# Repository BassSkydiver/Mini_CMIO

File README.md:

# CMIOBoard
A tiny, compact IO board for the raspberry compute modules 1/3/3+

## Features:
IO Ports:  
* USB-C (Power/USB 2.0)
* HDMI
* USB-Micro B (Slave port)
* Dual-USB-A 2.0
* Ethernet

## Other:
* Three pin 5V fan header
* Three pin boot selector
* 40 pin standard Raspberry Pi GPIO
* 4x2.2mm mounting holes
* Power LED (Red)
* Boot LED (Green)

## Dimensions:
75.66mm x 65.63mm  
2.844mm radius rounded corners
2.2mm diameter mounting holes (M2 or US #1/2 screws)  
69.97mm center distance between horizontally aligned mounting holes.  
59.94mm center distance between vertically aligned mounting holes.  
## Important!
The Raspberry Pi Compute Module requires a 5v, 2+ Amp power supply. (5.1V Recommended)
This board was made by a complete amatuer and should be avoided or subject to harsh scrutiny before used in a real application.

## Directions to Install:
1. Make sure your KiCAD verison is 7.0.6 or higher
2. Rename the "Footprints" folder to "Footprints.pretty"
3. Open the "RPCM1 IO Board.kicad_pro" file
4. Add symbols and footprints from this directory into the "Project Specific Libraries" section of the Symbol Library Manager and the Footprint Library Manager
5. Do whatever you want I guess :)

*License: GNU General Public License v3.0*  
*[gnu.org/licenses/gpl-3.0](https://www.gnu.org/licenses/gpl-3.0.en.html)*

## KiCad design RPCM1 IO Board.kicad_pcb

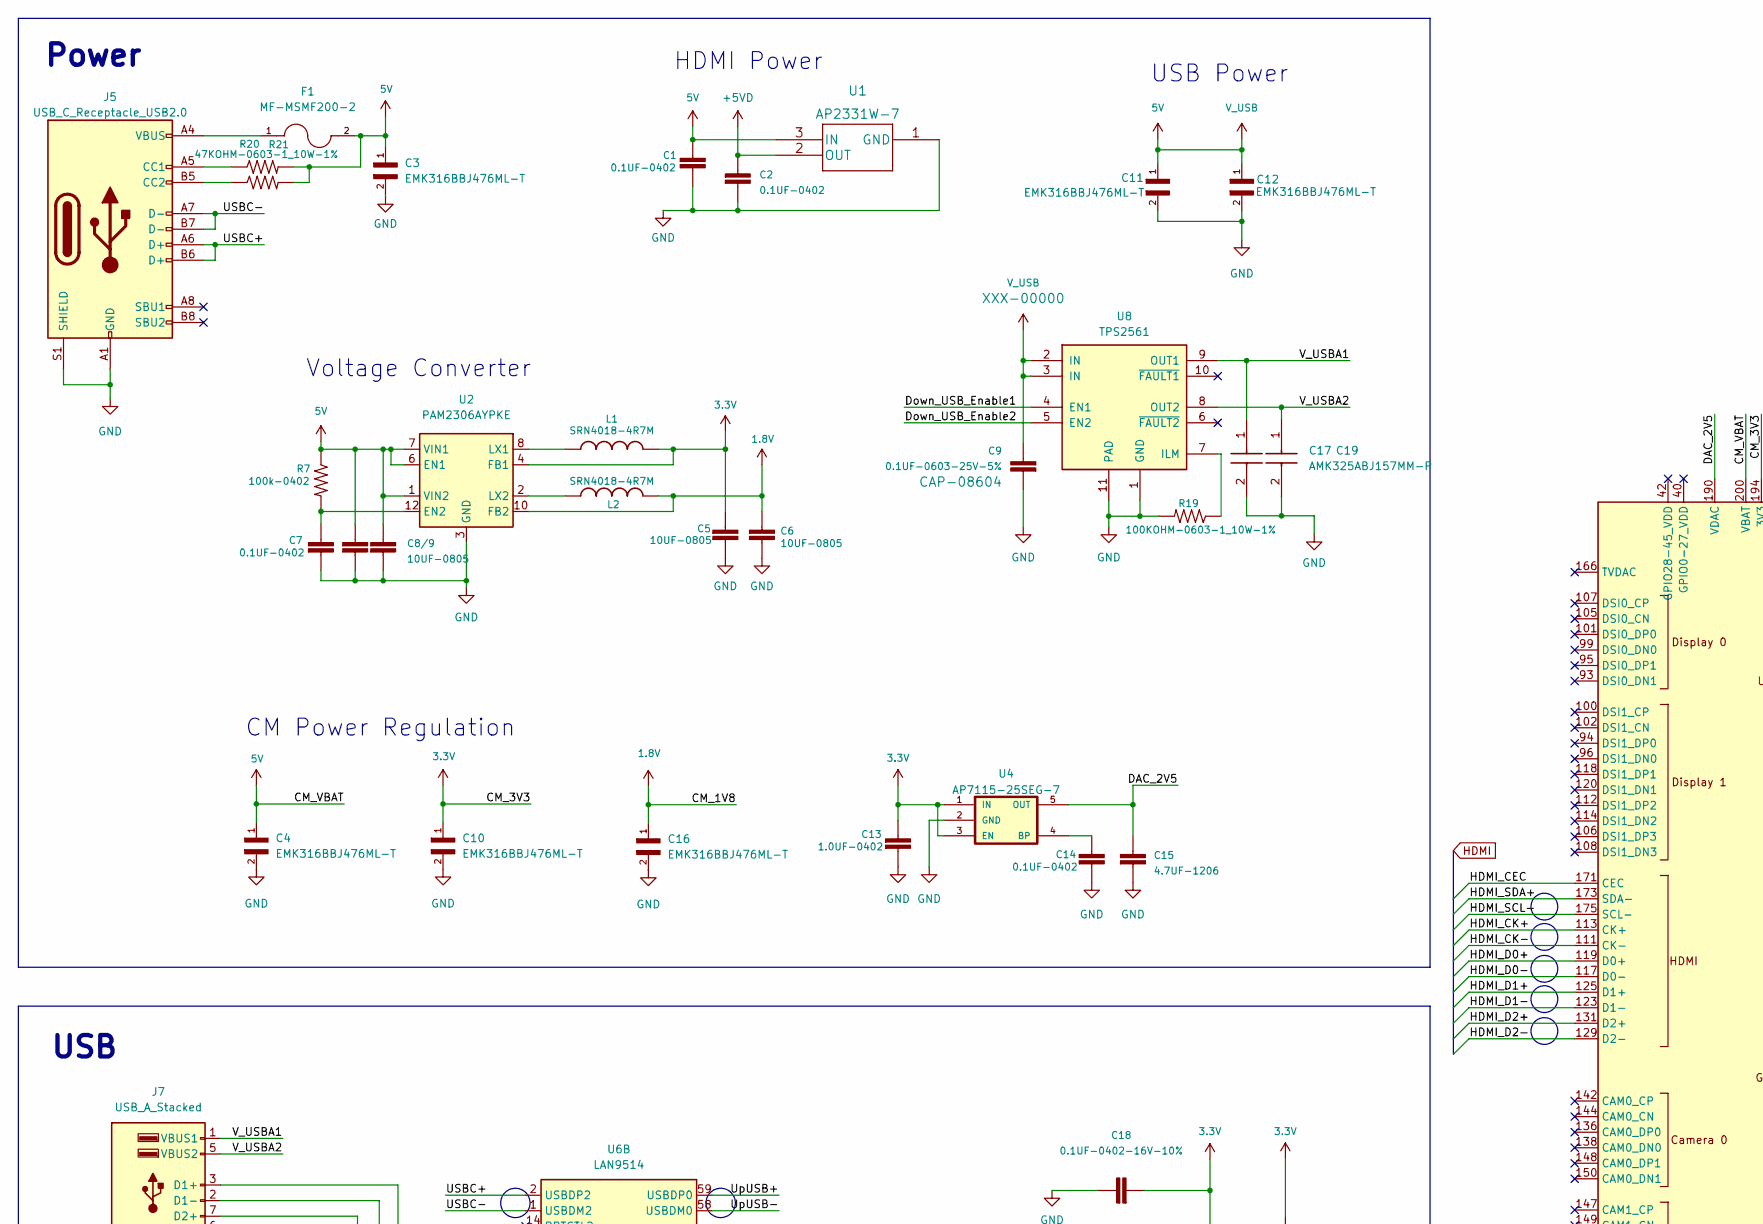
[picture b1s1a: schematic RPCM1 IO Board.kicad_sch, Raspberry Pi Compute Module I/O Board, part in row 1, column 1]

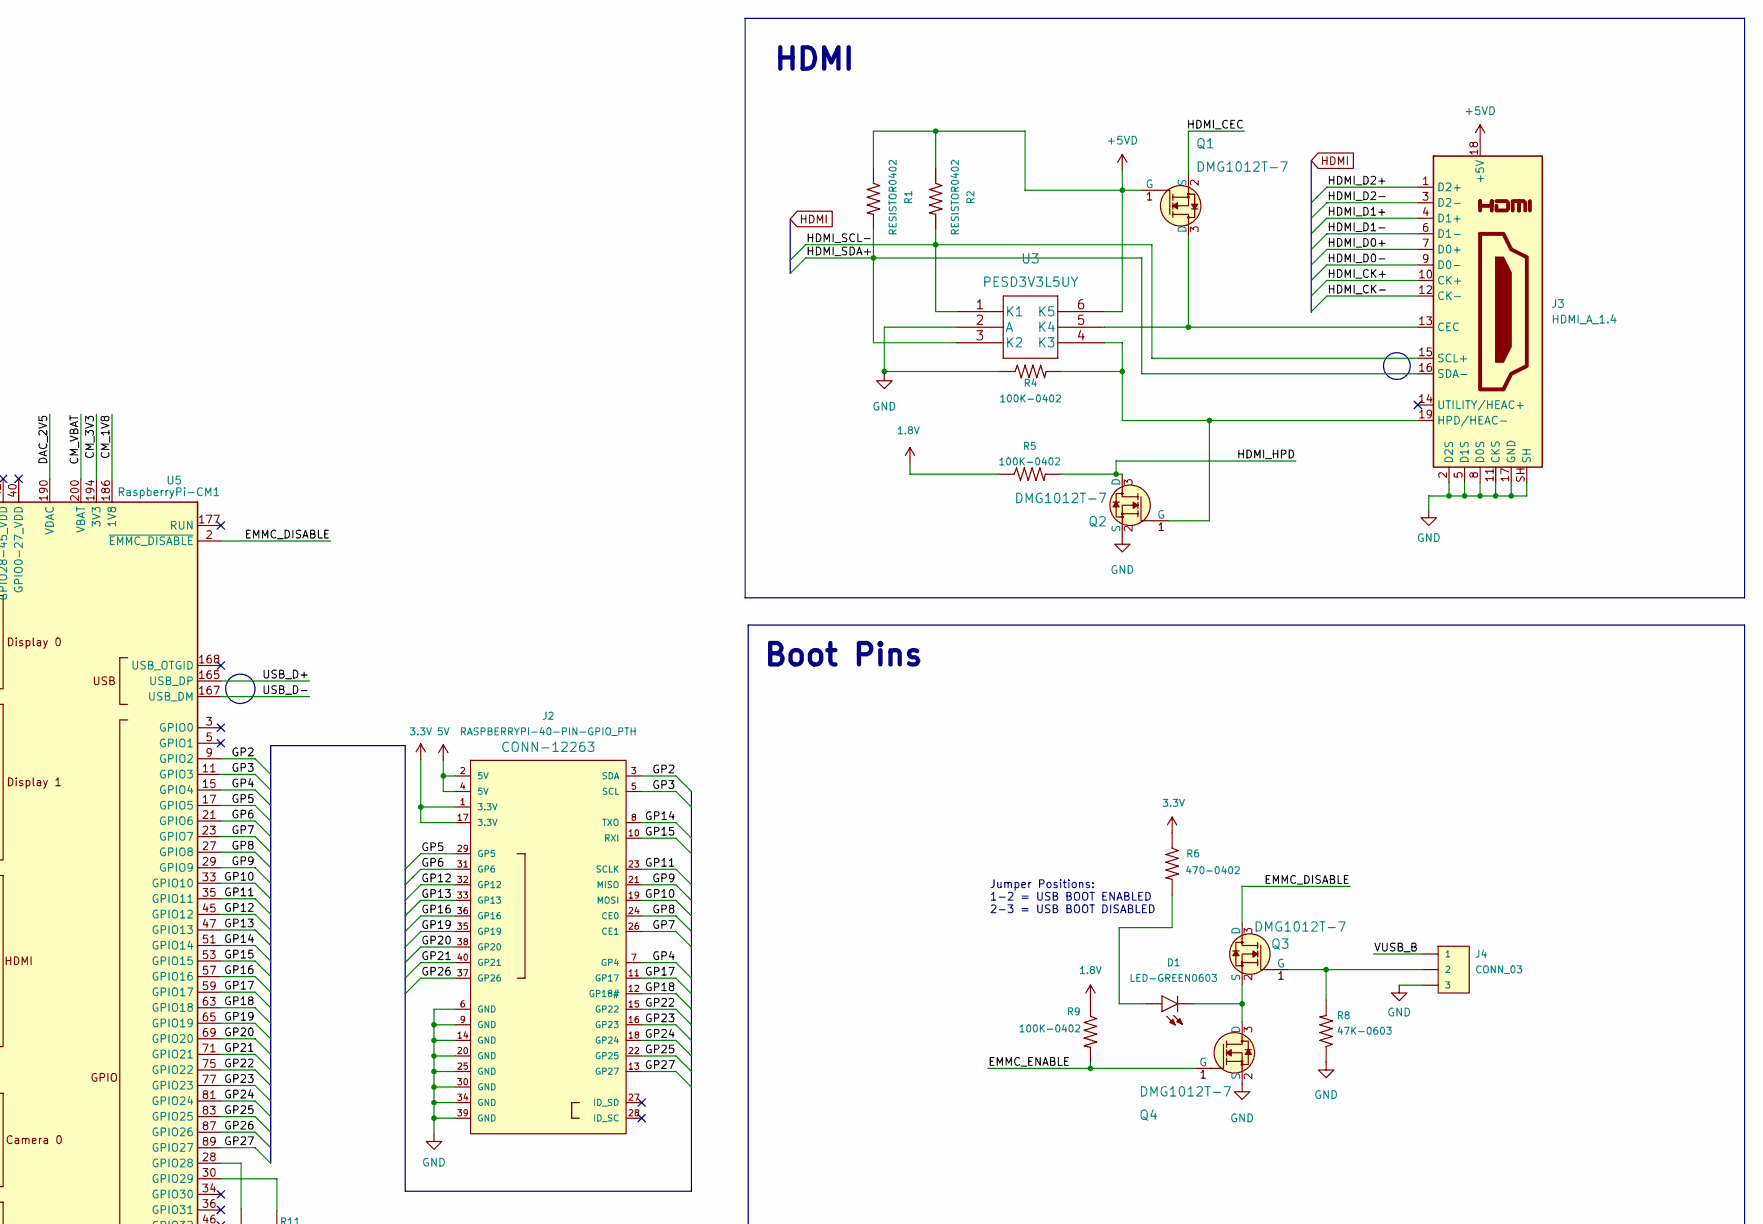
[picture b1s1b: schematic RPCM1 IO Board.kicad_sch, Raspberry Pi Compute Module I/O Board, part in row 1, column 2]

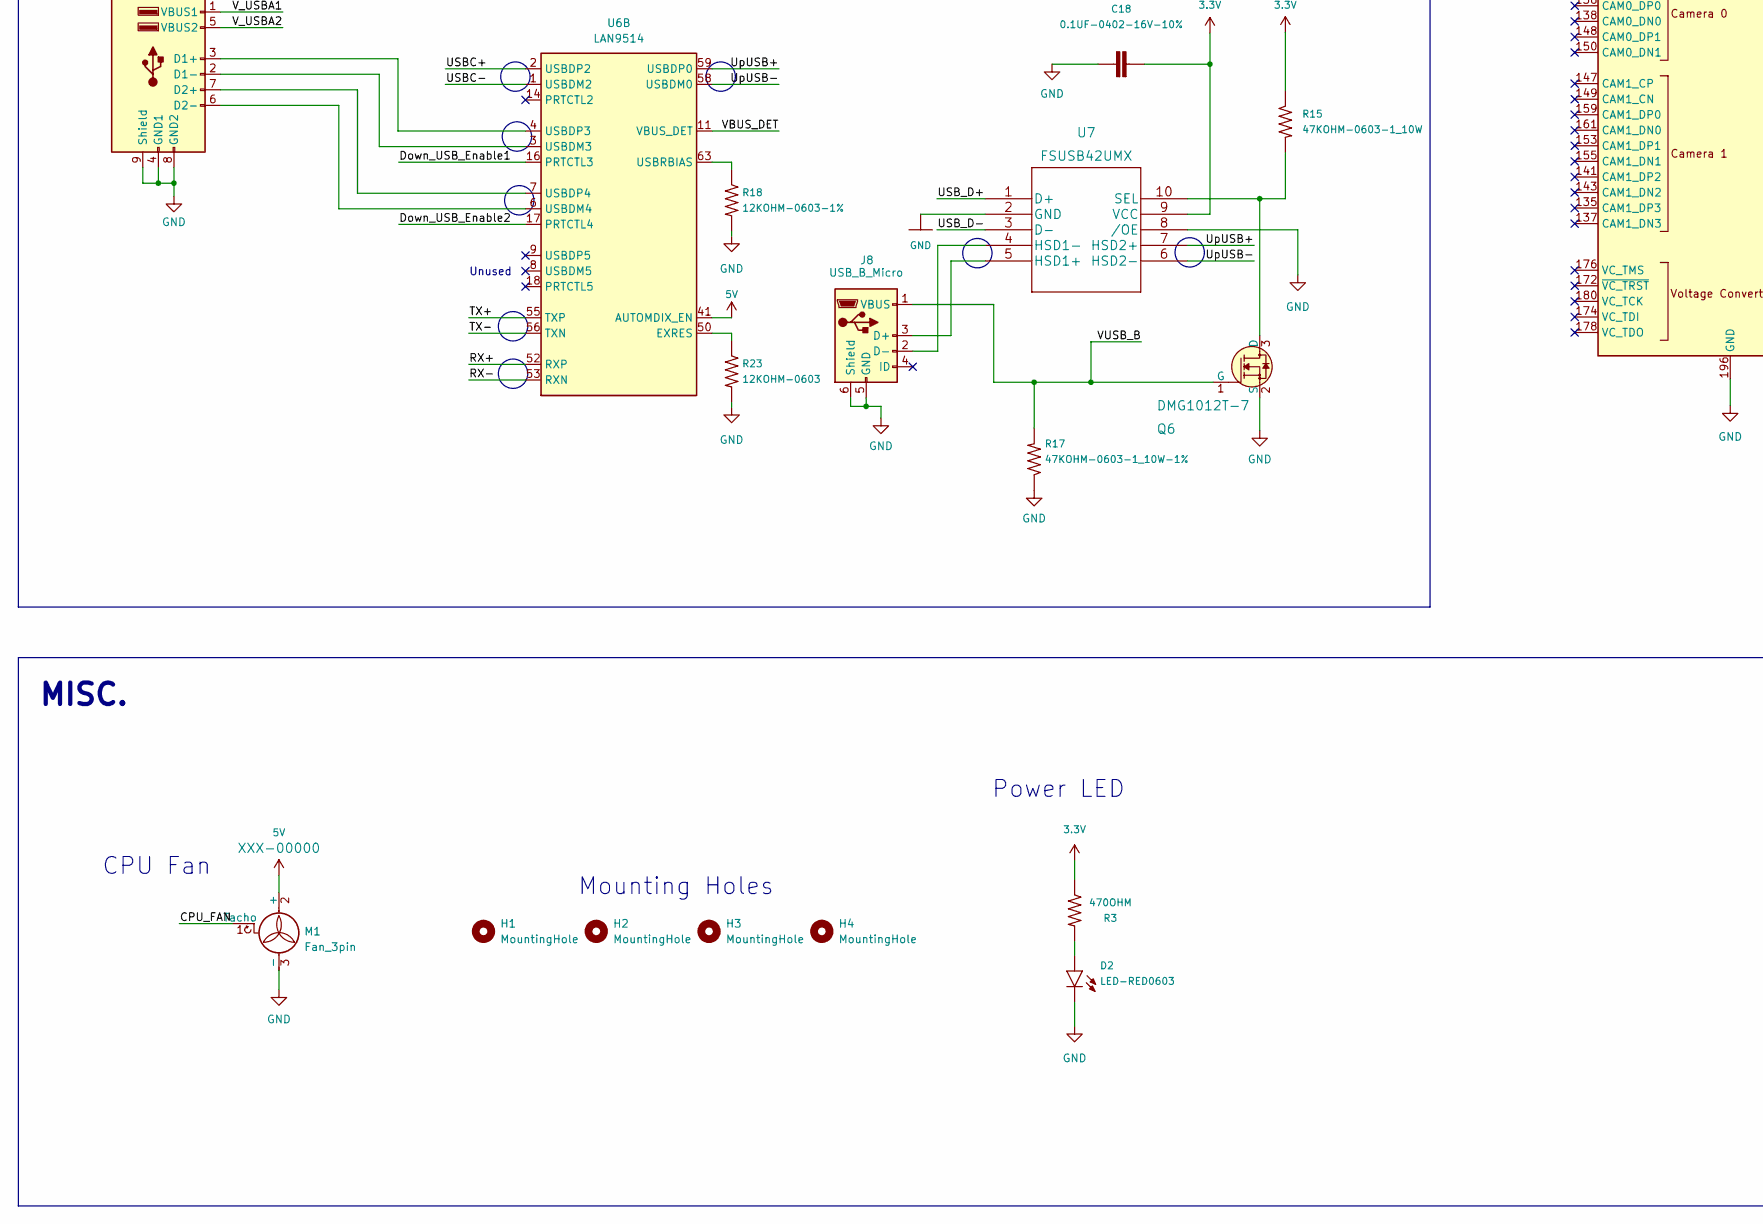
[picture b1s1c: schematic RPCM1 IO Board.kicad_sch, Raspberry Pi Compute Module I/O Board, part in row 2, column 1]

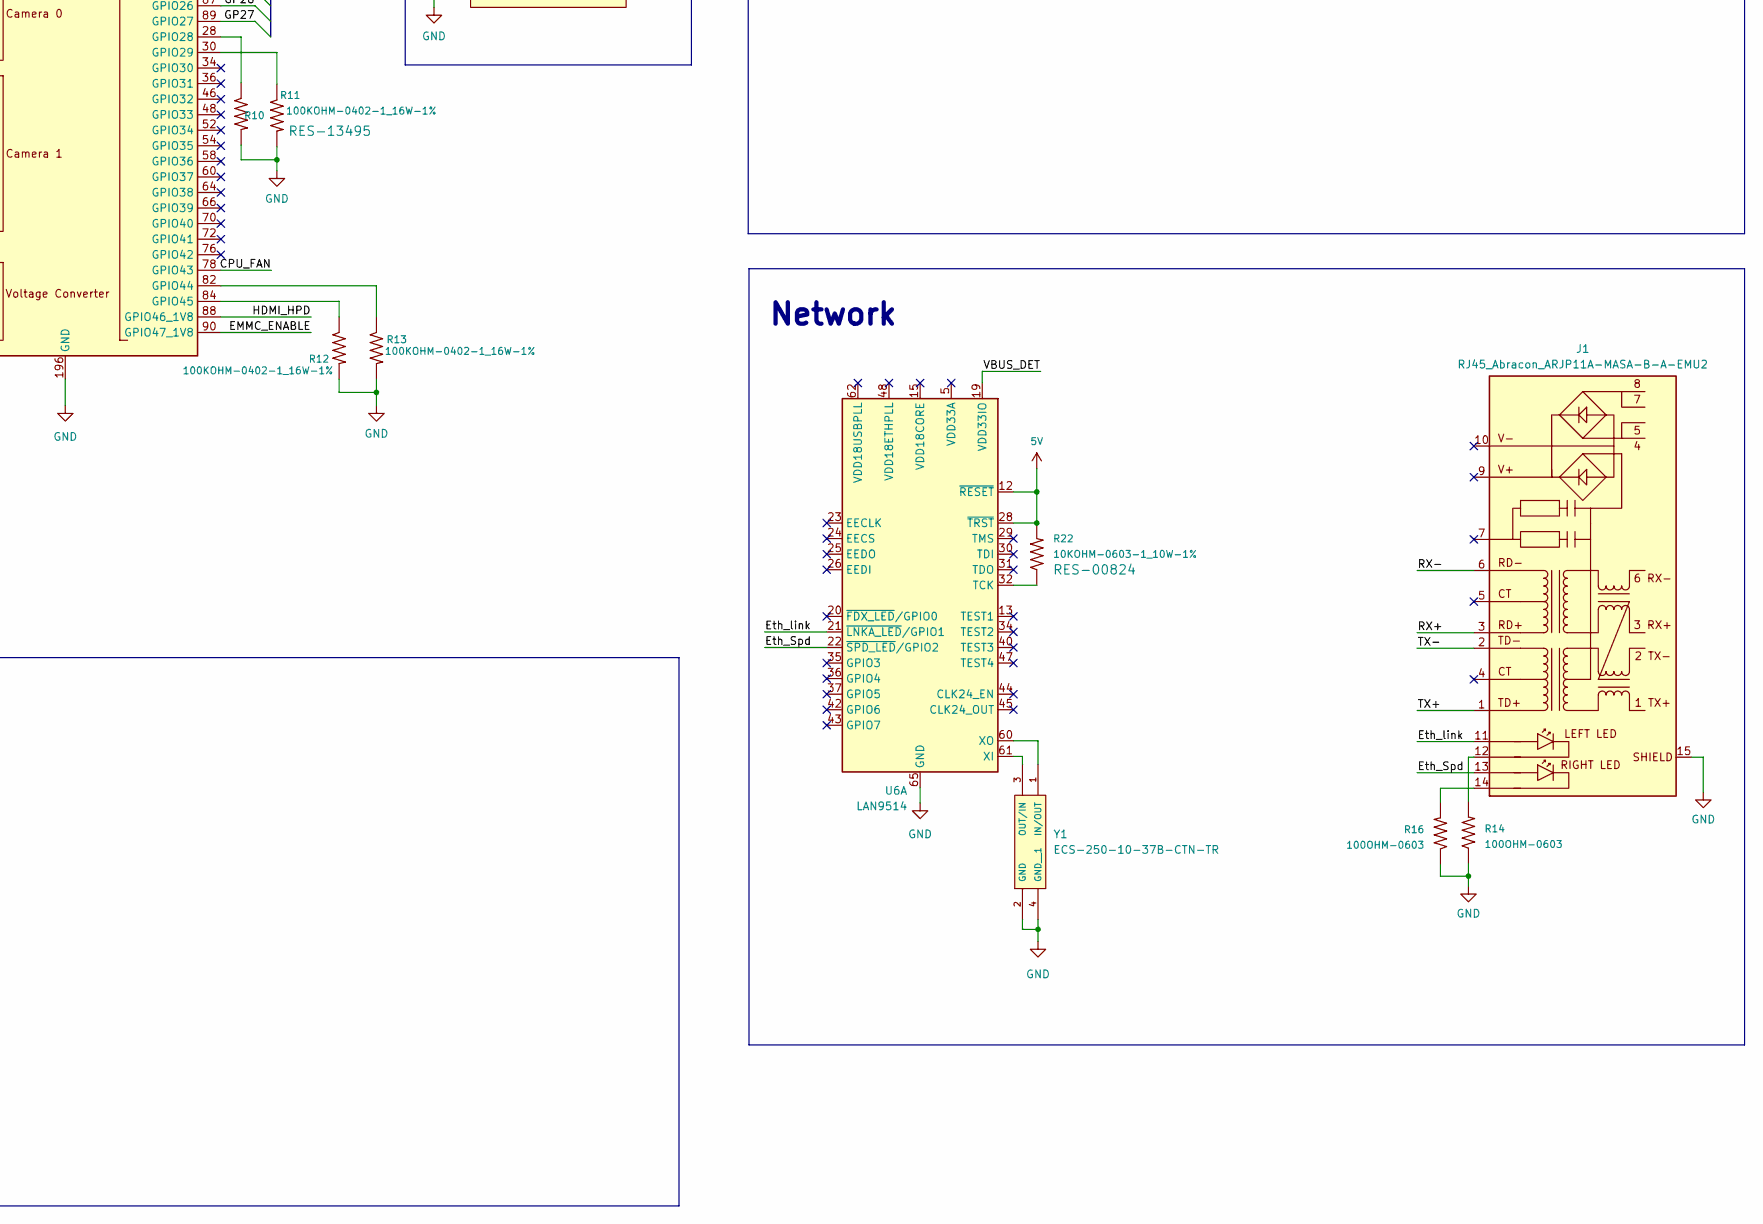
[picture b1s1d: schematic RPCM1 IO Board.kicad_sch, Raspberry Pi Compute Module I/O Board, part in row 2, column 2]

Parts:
C1, C2, C7, C14: 0.1UF-0402; 0402
C3, C4, C10, C11, C12, C16: EMK316BBJ476ML-T; CAPC3216X190N
C5, C6, C8/9: 10UF-0805; 0805
C8: 10UF-0805-10V-10%; 0805
C9: 0.1UF-0603-25V-5%; C_0603_1608Metric
C13: 1.0UF-0402; 0402
C15: 4.7UF-1206; 0603
C17, C19: AMK325ABJ157MM-P; 1210; Mouser Part Number 963-AMK325ABJ157MM-P
C18: 0.1UF-0402-16V-10%; 0402
D1: LED-GREEN0603; LED-0603
D2: LED-RED0603; LED-0603
F1: MF-MSMF200-2
H1, H2, H3, H4: MountingHole; MountingHole_2.2mm_M2_DIN965_Pad_TopBottom
J1: RJ45_Abracon_ARJP11A-MASA-B-A-EMU2; RJ45_Abracon_ARJP11A-MA_Horizontal
J2: RASPBERRYPI-40-PIN-GPIO_PTH; 2X20_NOSILK
J3: HDMI_A_1.4; HDMI_Mini_Female_2001-1-2-21-00-BK
J4: CONN_03; 1X03_NO_SILK
J5: USB_C_Receptacle_USB2.0; USB_C_Receptacle_GCT_USB4085
J7: USB_A_Stacked; USB_A_CUI_UJ2-ADH-TH_Horizontal_Stacked
J8: USB_B_Micro; USB_Micro_B_Female_10118193-0001LF
L1, L2: SRN4018-4R7M
M1: Fan_3pin; 1X03_NO_SILK
Q1, Q2, Q3, Q4, Q6: DMG1012T-7; SOT-523; MPN DMG1012T-7; Digi-Key_PN DMG1012T-7DICT-ND
R1, R2: RESISTOR0402; 0402
R3: 470OHM; 0402
R4, R5: 100K-0402; R_01005_0402Metric
R6: 470-0402; 0402
R7: 100k-0402; 0402
R8: 47K-0603; 0603
R9: 100K-0402; 0402
R10, R11, R12, R13: 100KOHM-0402-1_16W-1%; 0402
R14, R16: 100OHM-0603; R_0603_1608Metric
R15: 47KOHM-0603-1_10W; 0603
R17: 47KOHM-0603-1_10W-1%; 0603
R18: 12KOHM-0603-1%; R_0603_1608Metric
R19: 100KOHM-0603-1_10W-1%; R_0603_1608Metric
R20, R21: 47KOHM-0603-1_10W-1%; R_0603_1608Metric
R22: 10KOHM-0603-1_10W-1%; R_0603_1608Metric
R23: 12KOHM-0603; R_0603_1608Metric
U1: AP2331W-7
U2: PAM2306AYPKE; WDFN-12-1EP_3x3mm_P0.45mm_EP1.7x2.5mm
U3: PESD3V3L5UY
U4: AP7115-25SEG-7; AP7115-25SEG; PARTREV 12
U5: RaspberryPi-CM1; TE_1717254-4
U6: LAN9514; QFN-64-1EP_9x9mm_P0.5mm_EP7.3x7.3mm
U7: FSUSB42UMX
U8: TPS2561; VSON-10-1EP_3x3mm_P0.5mm_EP1.65x2.4mm_ThermalVias
Y1: ECS-250-10-37B-CTN-TR; CRYSTAL-SMD-3.2X2.5MM; PARTREV 2017

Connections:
1.8V: C6.1, C16.1, L2.1, R5.1, R9.1, U2.10 (FB2), U5.183 (1V8), U5.184 (1V8), U5.185 (1V8), U5.186 (1V8)
3.3V: C5.1, C10.1, C13.1, C18.2, J2.1 (3.3V), J2.17 (3.3V), L1.1, R3.1, R6.1, R15.1, U2.4 (FB1), U4.1 (IN), U4.3 (EN), U5.191 (3V3), U5.192 (3V3), U5.193 (3V3), U5.194 (3V3), U7.9 (VCC)
5V: C1.1, C3.1, C4.1, C8.1, C8/9.1, C9.1, C11.1, C12.1, F1.2, J2.2 (5V), J2.4 (5V), M1.2 (+), R7.1, R20.2, R21.2, R22.2, U1.3 (IN), U2.1 (VIN2), U2.6 (EN1), U2.7 (VIN1), U5.197 (VBAT), U5.198 (VBAT), U5.199 (VBAT), U5.200 (VBAT), U6.12 (~RESET), U6.28 (~TRST), U6.41 (AUTOMDIX_EN), U8.2 (IN), U8.3 (IN); also elsewhere on the board
+5VD: C2.1, J3.18 (+5V), Q1.1 (G), R1.1, R2.1, U1.2 (OUT), U3.6 (K5)
/CPU_FAN: M1.1 (Tacho), U5.78 (GPIO43)
/DAC_2V5: C15.1, U4.5 (OUT), U5.189 (VDAC), U5.190 (VDAC)
/Down_USB_Enable1: U6.16 (PRTCTL3), U8.4 (EN1)
/Down_USB_Enable2: U6.17 (PRTCTL4), U8.5 (EN2)
/EMMC_DISABLE: Q3.3 (D), U5.2 (~EMMC_DISABLE)
/EMMC_ENABLE: Q4.1 (G), R9.2, U5.90 (GPIO47_1V8)
/Eth_Spd: J1.13 (RLED+), U6.22 (~SPD_LED/GPIO2)
/Eth_link: J1.11 (LLED+), U6.21 (~LNKA_LED/GPIO1)
/GP2: J2.3 (SDA), U5.9 (GPIO2)
/GP3: J2.5 (SCL), U5.11 (GPIO3)
/GP4: J2.7 (GP4), U5.15 (GPIO4)
/GP5: J2.29 (GP5), U5.17 (GPIO5)
/GP6: J2.31 (GP6), U5.21 (GPIO6)
/GP7: J2.26 (CE1), U5.23 (GPIO7)
/GP8: J2.24 (CE0), U5.27 (GPIO8)
/GP9: J2.21 (MISO), U5.29 (GPIO9)
/GP10: J2.19 (MOSI), U5.33 (GPIO10)
/GP11: J2.23 (SCLK), U5.35 (GPIO11)
/GP12: J2.32 (GP12), U5.45 (GPIO12)
/GP13: J2.33 (GP13), U5.47 (GPIO13)
/GP14: J2.8 (TXO), U5.51 (GPIO14)
/GP15: J2.10 (RXI), U5.53 (GPIO15)
/GP16: J2.36 (GP16), U5.57 (GPIO16)
/GP17: J2.11 (GP17), U5.59 (GPIO17)
/GP18: J2.12 (GP18#), U5.63 (GPIO18)
/GP19: J2.35 (GP19), U5.65 (GPIO19)
/GP20: J2.38 (GP20), U5.69 (GPIO20)
/GP21: J2.40 (GP21), U5.71 (GPIO21)
/GP22: J2.15 (GP22), U5.75 (GPIO22)
/GP23: J2.16 (GP23), U5.77 (GPIO23)
/GP24: J2.18 (GP24), U5.81 (GPIO24)
/GP25: J2.22 (GP25), U5.83 (GPIO25)
/GP26: J2.37 (GP26), U5.87 (GPIO26)
/GP27: J2.13 (GP27), U5.89 (GPIO27)
/HDMI_CEC: Q1.2 (S), U5.171 (CEC)
/HDMI_CK+: J3.10 (CK+), U5.113 (CK+)
/HDMI_CK-: J3.12 (CK-), U5.111 (CK-)
/HDMI_D0+: J3.7 (D0+), U5.119 (D0+)
/HDMI_D0-: J3.9 (D0-), U5.117 (D0-)
/HDMI_D1+: J3.4 (D1+), U5.125 (D1+)
/HDMI_D1-: J3.6 (D1-), U5.123 (D1-)
/HDMI_D2+: J3.1 (D2+), U5.131 (D2+)
/HDMI_D2-: J3.3 (D2-), U5.129 (D2-)
/HDMI_HPD: Q2.3 (D), R5.2, U5.88 (GPIO46_1V8)
/HDMI_SCL: J3.15 (SCL+), R2.2, U3.1 (K1), U5.175 (SCL-)
/HDMI_SDA: J3.16 (SDA-), R1.2, U3.3 (K2), U5.173 (SDA-)
/RX+: J1.3 (RD+), U6.52 (RXP)
/RX-: J1.6 (RD-), U6.53 (RXN)
/TX+: J1.1 (TD+), U6.55 (TXP)
/TX-: J1.2 (TD-), U6.56 (TXN)
/USBC+: J5.A6 (D+), J5.B6 (D+), U6.2 (USBDP2)
/USBC-: J5.A7 (D-), J5.B7 (D-), U6.1 (USBDM2)
/USB_D+: U5.165 (USB_DP), U7.1 (D+)
/USB_D-: U5.167 (USB_DM), U7.3 (D-)
/UpUSB+: U6.59 (USBDP0), U7.7 (HSD2+)
/UpUSB-: U6.58 (USBDM0), U7.6 (HSD2-)
/VBUS_DET: U6.11 (VBUS_DET), U6.19 (VDD33IO), U6.27 (VDD33IO), U6.33 (VDD33IO), U6.39 (VDD33IO), U6.46 (VDD33IO)
/VUSB_B: J4.1, J8.1 (VBUS), Q6.1 (G), R17.2
/V_USBA1: C19.1, J7.1 (VBUS1), U8.9 (OUT1)
/V_USBA2: C17.1, J7.5 (VBUS2), U8.8 (OUT2)
GND: C1.2, C2.2, C3.2, C4.2, C5.2, C6.2, C7.2, C8.2, C8/9.2, C9.2, C10.2, C11.2, C12.2, C13.2, C14.2, C15.2, C16.2, C17.2, C18.1, C19.2, D2.C, J1.15 (SHIELD), J2.6 (GND), J2.9 (GND), J2.14 (GND), J2.20 (GND), J2.25 (GND), J2.30 (GND), J2.34 (GND), J2.39 (GND), J3.2 (D2S), J3.5 (D1S), J3.8 (D0S), J3.11 (CKS), J3.17 (GND), J3.SH, J4.3, J5.A1 (GND), J5.A12 (GND), J5.B1 (GND), J5.B12 (GND), J5.S1 (SHIELD), J7.4 (GND1), J7.8 (GND2), J7.9 (Shield), J8.5 (GND), J8.6 (Shield), M1.3 (-), Q2.2 (S), Q4.2 (S), Q6.2 (S), R4.1, R8.1, R10.2, R11.2, R12.2, R13.2, R14.1, R16.1, R17.1, R18.2, R19.2, R23.2, U1.1 (GND), U2.3 (GND), U2.9 (GND), U2.13 (GND), U3.2 (A), U4.2 (GND), U5.1 (GND), U5.7 (GND), U5.13 (GND), U5.19 (GND), U5.25 (GND), U5.26 (GND), U5.31 (GND), U5.32 (GND), U5.37 (GND), U5.38 (GND), U5.43 (GND), U5.44 (GND), U5.49 (GND), U5.50 (GND), U5.55 (GND), U5.56 (GND), U5.61 (GND), U5.62 (GND), U5.67 (GND), U5.68 (GND), U5.73 (GND), U5.74 (GND), U5.79 (GND), U5.80 (GND), U5.85 (GND), U5.86 (GND), U5.91 (GND), U5.92 (GND), U5.97 (GND), U5.98 (GND), U5.103 (GND), U5.104 (GND), U5.109 (GND), U5.110 (GND), U5.115 (GND), U5.116 (GND), U5.121 (GND), U5.122 (GND), U5.127 (GND), U5.133 (GND), U5.134 (GND), U5.139 (GND), U5.140 (GND), U5.145 (GND), U5.146 (GND), U5.151 (GND), U5.152 (GND), U5.157 (GND), U5.163 (GND), U5.164 (GND), U5.169 (GND), U5.170 (GND), U5.181 (GND), U5.182 (GND), U5.187 (GND), U5.188 (GND), U5.195 (GND), U5.196 (GND), U6.65 (GND), U7.2 (GND), U7.8 (/OE), U8.1 (GND), U8.11 (PAD), Y1.2 (GND), Y1.4 (GND__1); also elsewhere on the board
J7-D1+: J7.3 (D1+), U6.4 (USBDP3)
J7-D1-: J7.2 (D1-), U6.3 (USBDM3)
J7-D2+: J7.7 (D2+), U6.7 (USBDP4)
J7-D2-: J7.6 (D2-), U6.6 (USBDM4)
J8-D+: J8.3 (D+), U7.5 (HSD1+)
J8-D-: J8.2 (D-), U7.4 (HSD1-)
unnamed: D1.A, R6.2
unnamed: D2.A, R3.2
unnamed: F1.1, J5.A4 (VBUS), J5.A9 (VBUS), J5.B4 (VBUS), J5.B9 (VBUS)
unnamed: J1.12 (LLED-), R14.2
unnamed: J1.14 (RLED-), R16.2
unnamed: J3.13 (CEC), Q1.3 (D), U3.5 (K4)
unnamed: J3.19 (HPD/HEAC-), Q2.1 (G), R4.2, U3.4 (K3)
unnamed: J5.A5 (CC1), R20.1
unnamed: J5.B5 (CC2), R21.1
unnamed: J4.2, Q3.1 (G), R8.2
unnamed: D1.C, Q3.2 (S), Q4.3 (D)
unnamed: Q6.3 (D), R15.2, U7.10 (SEL)
unnamed: C7.1, R7.2, U2.12 (EN2)
unnamed: L1.2, U2.8 (LX1)
unnamed: L2.2, U2.2 (LX2)
unnamed: C14.1, U4.4 (BP)
unnamed: R10.1, U5.28 (GPIO28)
unnamed: R11.1, U5.30 (GPIO29)
unnamed: R13.1, U5.82 (GPIO44)
unnamed: R12.1, U5.84 (GPIO45)
unnamed: R22.1, U6.32 (TCK)
unnamed: R23.1, U6.50 (EXRES)
unnamed: R18.1, U6.63 (USBRBIAS)
unnamed: R19.1, U8.7 (ILM)
U6A-XI: U6.61 (XI), Y1.3 (OUT/IN)
\U6A-XO: U6.60 (XO), Y1.1 (IN/OUT)

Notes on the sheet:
Boot Pins
HDMI
USB
CPU Fan
USB Power
MISC.
Jumper Positions: 1-2 = USB BOOT ENABLED 2-3 = USB BOOT DISABLED
Network
Power
Mounting Holes
HDMI Power
Power LED
Voltage Converter
CM Power Regulation
Unused

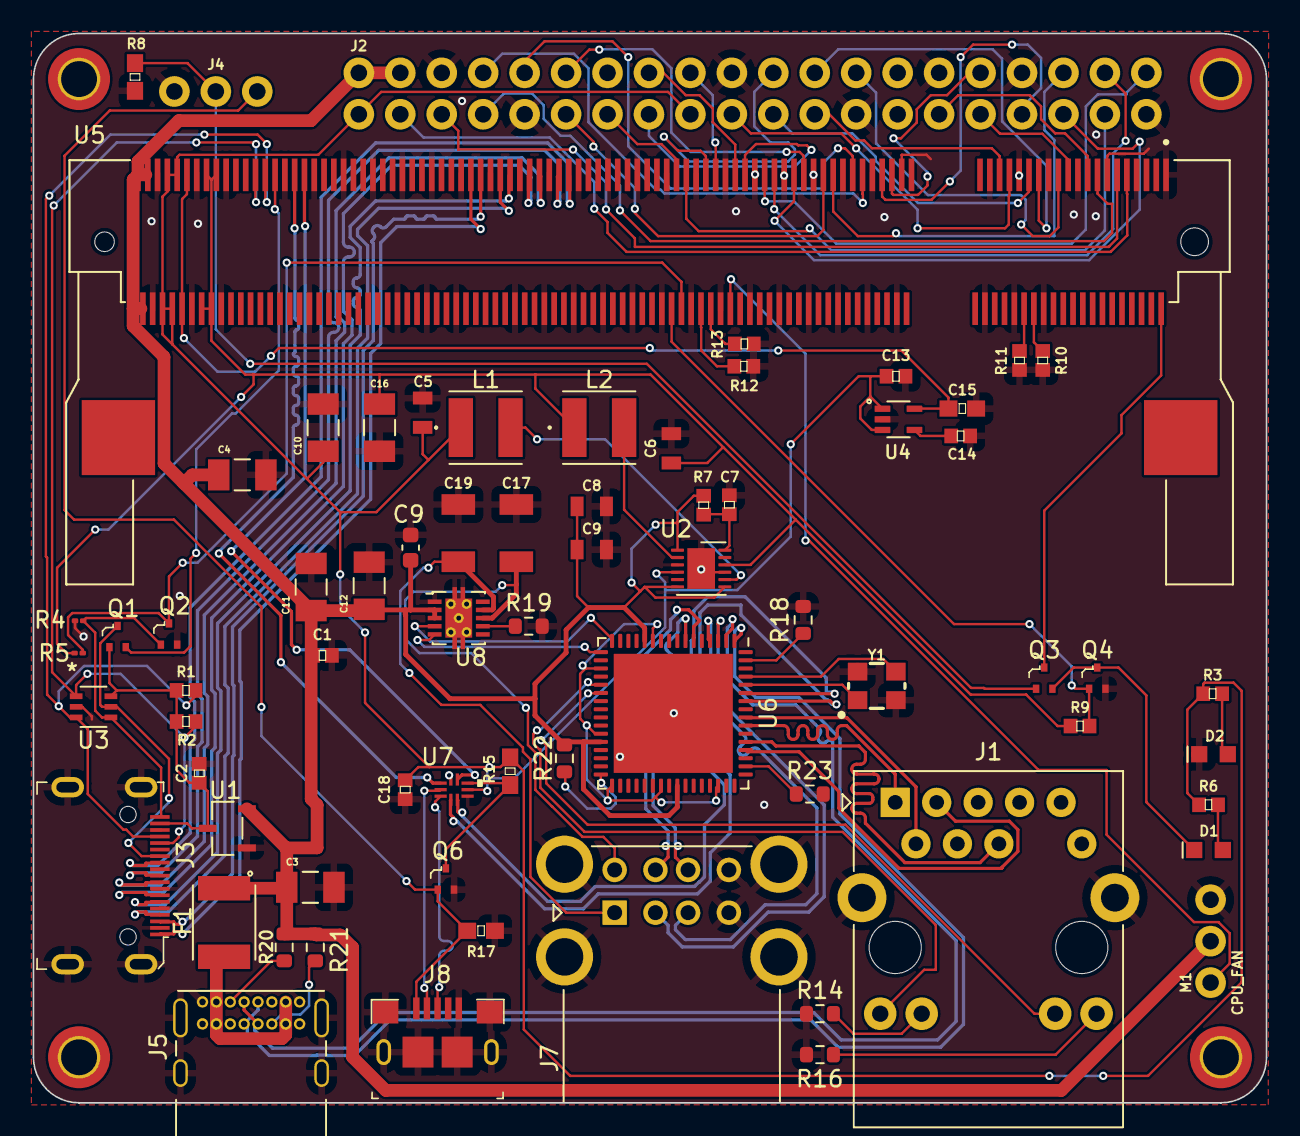
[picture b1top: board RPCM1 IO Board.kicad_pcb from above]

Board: 2 copper layers, 75.6 x 65.5 mm, 74 parts (0 on the bottom side), 97 nets.

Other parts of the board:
C9#2: 0.1UF-0603-25V-5%; C_0603_1608Metric

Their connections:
5V: C9#2.1; also elsewhere on the board
GND: C9#2.2; also elsewhere on the board

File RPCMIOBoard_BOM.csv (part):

Source:,C:\Users\natha\OneDrive\Documents\PCB Designs\RPCM1 IO Board\RPCM1 IO Board.kicad_sch,,,,,,,,
Date:,1/9/2023 3:18:24 PM,,,,,,,,
Tool:,Eeschema (6.0.9),,,,,,,,
Generator:,C:\Program Files\KiCad\6.0\bin\scripting\plugins/bom_csv_grouped_by_value_with_fp.py,,,,,,,,
Component Count:,60,,,,,,,,
Ref,Qnty,Cmp name,DK Name,Description,Datasheet,Manufacturer,DK Link,Price (Single),Price (Total)
"C1, C2, C6, C12, C14, ",5,0.1UF-0402-16V-10%,04026D104KAT2A,0.1 µF ±10% 6.3V Ceramic Capacitor X5R 0402 (1005 Metric),https://datasheets.kyocera-avx.com/cx5r.pdf,KYOCERA AVX,https://www.digikey.com/en/products/detail/kyocera-avx/04026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,$0.10,$0.50
"C3, C9, C10, C15, C16, C17, ",6,EMK316BBJ476ML-T,CL31A476MQHNNWE,CAP CER 0.1UF 6.3V X5R 0402,https://www.samsungsem.com/kr/support/product-search/mlcc/CL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,Samsung Electro-Mechanics,https://www.digikey.com/en/products/detail/samsung-electro-m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,$0.41,$2.46
"C4, C5, C7, C8, ",4,10UF-0805-10V-10%,CL21A106KOQNNNE,CAP CER 10UF 16V X5R 0805,https://media.digikey.com/pdf/Data%20Sheets/Samsung%20PDFs/C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,Samsung Electro-Mechanics,https://www.digikey.com/en/products/detail/samsung-electro-m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,$0.10,$0.40
"C11, ",1,1.0UF-0402-16V-10%,CC0402KRX5R5BB105,CAP CER 1UF 6.3V X5R 0402,https://www.yageo.com/upload/media/product/productsearch/dat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,YAGEO,https://www.digikey.com/en/products/detail/yageo/CC0402KRX5R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,$0.11,$0.11
"C13, ",1,4.7UF-1206-16V-_+80_-20%_,CL10A475KP8NNNC,CAP CER 4.7UF 10V X5R 0603,https://media.digikey.com/pdf/Data%20Sheets/Samsung%20PDFs/C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,Samsung Electro-Mechanics,https://www.digikey.com/en/products/detail/samsung-electro-m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,$0.10,$0.10
"D1, ",1,LED-GREEN0603,LTST-C191KGKT,LED GREEN CLEAR SMD,https://optoelectronics.liteon.com/upload/download/DS22-2000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,Lite-On Inc.,https://www.digikey.com/en/products/detail/liteon/LTST-C191K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,$0.26,$0.26
"D2, ",1,LED-RED0603,SML-D12U8WT86,Red 620nm LED Indication - Discrete 2.2V 0603 (1608 Metric),https://fscdn.rohm.com/en/products/databook/datasheet/opto/l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,Rohm Semiconductor,https://www.digikey.com/en/products/detail/rohm-semiconducto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,$0.37,$0.37
"F1, ",1,MF-MSMF200-2,MF-MSMF200-2,"Polymeric PTC Resettable Fuse 8V 2 A Ih Surface Mount 1812 (4532 Metric), Concave",https://www.bourns.com/docs/product-datasheets/mf-msmf.pdf,Bourns Inc.,https://www.digikey.com/en/products/detail/bourns-inc/MF-MSM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,$0.61,$0.61
"H1, H2, H3, H4, ",4,MountingHole,x,Grounded Mounting Hole,x,x,x,x,x
"J1, ",1,USB4085-GF-A,USB4085-GF-A,"USB-C (USB TYPE-C) USB 2.0 Receptacle Connector 24 (16+8 Dummy) Position Through Hole, Right Angle",https://gct.co/files/drawings/usb4085.pdf,GCT,https://www.digikey.com/en/products/detail/gct/USB4085-GF-A/9859662,$0.94,$0.94
"J2, ",1,HDMI_A_1.4,10029449-111RLF,"HDMI HDMI 1.4 Receptacle Connector 19 Position Surface Mount, Right Angle; Through Hole",https://www.amphenol-cs.com/media/wysiwyg/files/drawing/1002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,Amphenol ICC (FCI),https://www.digikey.com/en/products/detail/amphenol-cs-fci/1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,$1.26,$1.26
"J3, ",1,CONN_02POGO_PIN_HOLES_ONLY,61300211121,CONN HEADER VERT 2POS 2.54MM,https://www.we-online.com/katalog/datasheet/6130xx11121.pdf,Würth Elektronik,https://www.digikey.com/en/products/detail/w%C3%BCrth-elektr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,$0.13,$0.13
"J4, ",1,CONN_03,M20-9990345,"Connector Header Through Hole 3 position 0.100"" (2.54mm)",https://cdn.harwin.com/pdfs/C001XX_M20_Series_Connectors.pdf,Harwin Inc.,https://www.digikey.com/en/products/detail/harwin-inc/M20-99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,$0.19,$0.19
"J5, ",1,USB_A,1002-021-01000,USB-A (USB TYPE-A) USB 2.0 Receptacle Connector 4 Position Through Hole,http://www.cnctech.us/pdfs/1002-021-01000.pdf,CNC Tech,https://www.digikey.com/en/products/detail/cnc-tech/1002-021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,$1.11,$1.11
"J6, ",1,USB_A,87520-0010BLF,"USB-A (USB TYPE-A) USB 2.0 Receptacle Connector 4 Position Through Hole, Right Angle",https://www.amphenol-cs.com/media/wysiwyg/files/drawing/87520.pdf,Amphenol ICC (FCI),https://www.digikey.com/en/products/detail/amphenol-cs-fci/8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,$0.95,$0.95
"J7, ",1,USB_B_Micro,10118193-0001LF,"USB - micro B USB 2.0 Receptacle Connector 5 Position Surface Mount, Right Angle; Through Hole",https://cdn.amphenol-cs.com/media/wysiwyg/files/documentatio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,Amphenol ICC (FCI),https://www.digikey.com/en/products/detail/amphenol-cs-fci/1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,$0.46,$0.46
"L1, L2, ",2,SRN4018-4R7M,SRN4018-4R7M,"4.7 µH Semi-Shielded Drum Core, Wirewound Inductor 1.9 A 84mOhm Max Nonstandard",https://www.bourns.com/docs/Product-Datasheets/SRN4018.pdf,Bourns Inc.,https://www.digikey.com/en/products/detail/bourns-inc/SRN401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,$0.50,$1.00
"M1, ",1,Fan_CPU_4pin,640452-4,"Connector Header Through Hole 4 position 0.100"" (2.54mm)",https://www.te.com/commerce/DocumentDelivery/DDEController?A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,TE Connectivity AMP Connectors,https://www.digikey.com/en/products/detail/te-connectivity-a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,$0.66,$0.66
"Q1, Q2, Q3, Q4, Q5, ",5,DMG1012T-7,DMG1012T-7,N-Channel 20 V 630mA (Ta) 280mW (Ta) Surface Mount SOT-523,https://www.diodes.com/assets/Datasheets/DMG1012T.pdf,Diodes Incorporated,https://www.digikey.com/en/products/detail/diodes-incorporat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,$0.33,$1.65
"R1, R2, ",2,RESISTOR0402,RC0402FR-071K74L,"1.74 kOhms ±1% 0.063W, 1/16W Chip Resistor 0402 (1005 Metric) Moisture Resistant Thick Film",https://www.yageo.com/upload/media/product/productsearch/dat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,YAGEO,https://www.digikey.com/en/products/detail/yageo/RC0402FR-07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,$0.10,$0.20
"R3, R5, R4, R8, R9, R10, R12, R13, ",8,100KOHM-0402-1_16W-1%,RC0402FR-07100KL,"100 kOhms ±1% 0.063W, 1/16W Chip Resistor 0402 (1005 Metric) Moisture Resistant Thick Film",https://www.yageo.com/upload/media/product/productsearch/dat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,YAGEO,https://www.digikey.com/en/products/detail/yageo/RC0402FR-07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,$0.10,$0.80
"R6, R15, ",2,470OHM,RC0402FR-07470RL,"470 Ohms ±1% 0.063W, 1/16W Chip Resistor 0402 (1005 Metric) Moisture Resistant Thick Film",https://www.yageo.com/upload/media/product/productsearch/dat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,YAGEO,https://www.digikey.com/en/products/detail/yageo/RC0402FR-07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,$0.10,$0.20
"R7, R11, R14, ",3,47KOHM-0603-1_10W-1%,RC0603FR-0747KL,"47 kOhms ±1% 0.1W, 1/10W Chip Resistor 0603 (1608 Metric) Moisture Resistant Thick Film",https://www.yageo.com/upload/media/product/productsearch/dat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,YAGEO,https://www.digikey.com/en/products/detail/yageo/RC0603FR-07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,$0.10,$0.30
"U1, ",1,AP2331W-7,AP2331W-7,Current Switch Regulator High-Side 200mA SC-59-3,https://www.diodes.com/assets/Datasheets/AP2331.pdf,Diodes Incorporated,https://www.digikey.com/en/products/detail/diodes-incorporat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,$0.43,$0.43
"U2, ",1,PESD3V3L5UY,"PESD3V3L5UY,115",12V Clamp 2.5A (8/20µs) Ipp Tvs Diode Surface Mount 6-TSSOP,https://assets.nexperia.com/documents/data-sheet/PESDXL5UF_V_Y.pdf,Nexperia USA Inc.,https://www.digikey.com/en/products/detail/nexperia-usa-inc/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,$0.43,$0.43
"U3, ",1,PAM2306AYPKE,PAM2306AYPKE,"Buck Switching Regulator IC Positive Fixed 1.8V, 3.3V 2 Output 1A 12-WFDFN Exposed Pad",https://www.diodes.com/assets/Datasheets/PAM2306.pdf,Diodes Incorporated,https://www.digikey.com/en/products/detail/diodes-incorporat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,$0.76,$0.76
"U4, ",1,AP7115-25SEG-7,AP7115-25SEG-7,Linear Voltage Regulator IC Positive Fixed 1 Output 150mA SOT-353,https://media.digikey.com/pdf/Data%20Sheets/Diodes%20PDFs/AP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,Diodes Incorporated,https://www.digikey.com/en/products/detail/diodes-incorporat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,$0.42,$0.42
"U5, ",1,RaspberryPi-CM1,1717254-4,"200 Position SODIMM DDR2 SDRAM Socket Surface Mount, Right Angle",https://www.te.com/commerce/DocumentDelivery/DDEController?A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,TE Connectivity AMP Connectors,https://www.digikey.com/en/products/detail/te-connectivity-a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,$7.91,$7.91
"U6, ",1,FSUSB42UMX,FSUSB42UMX,USB Switch IC 1 Channel 10-UMLP (1.8x1.4),https://rocelec.widen.net/view/pdf/a7amyaouts/FAIR-S-A000117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,onsemi,https://www.digikey.com/en/products/detail/onsemi/FSUSB42UMX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,$0.75,$0.75
,,,,,,,,,$25.36
External Parts:,11,,,,,,,,
Type,Qnty,Cmp name,DK Name,Description,Datasheet,Manufacturer,DK Link,Price (Single),Price (Total)
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
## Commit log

2023-01-11 Added Schematic/Gerber Files
2023-01-11 Added PCB images
2023-01-11 Created README
2023-01-11 Uploaded BOM
2023-01-11 Rename RPCM1 IO Board.csv to RPCMIOBoard_BOM.csv
2023-01-11 Updated Todo List
2023-01-11 Added Todo items
2023-01-11 Added Issues table and updated Todo list
2023-01-11 Added PDFs and Gerbers
2023-01-11 Temporary files
2023-01-11 Created Gerber folder
2023-01-11 Deleted redundant Gerber files
2023-01-11 Deleted temporary files
2023-01-11 Deleted PDF files
2023-01-11 created temporary files
2023-01-11 Added PCB rendered images
2023-01-11 Deleted Images
2023-01-11 Updated Image directory
2023-01-17 Updated license
2023-01-19 Deleted temporary.md
2023-01-19 Added 3d renders
2023-01-19 Updated images
2023-06-23 Added images of raw and assembled board
2023-06-23 Update README.md
    added new images and updated TODO list
2023-07-09 Update README.md again
2023-08-09 Added new files
2023-08-09 Create a
2023-08-09 Added disclaimer
2023-08-22 Create
2023-08-22 Update and rename Footprints.pretty to Footprints/a
2023-08-22 Added Footprints
2023-08-22 added symbols
2023-08-22 Update README.md with instructions
    Added steps for instillation that instruct the user to rename the footprints folder and add the symbols/footprints to their project specific libraries.

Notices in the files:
RPCM1 IO Board.kicad_pcb:
creativecommons.org/licenses/by/4.0
License: CC BY 4.0
parts and their libraries:
Released under the Creative Commons Attribution Share-Alike 4.0 License
https://creativecommons.org/licenses/by-sa/4.0
